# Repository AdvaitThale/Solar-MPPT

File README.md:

# Solar-MPPT
***************************************************************
The basic functionality of the device is based on previous generation Solar MPPTs, but it is fully autonomous (alpha ver) using ESP32 as microcontroller.
The file named `MPPT_Port-Xtensa.ino` code is final port of MPPT on the ESP32. Also, `MPPT_Port-328P.ino` shows an overview of how MPPT will work with ATMega328P microcontroller (with reduced functionality).It is equipped with 20*4 Character LCD (for device & energy status), Function Buttons, ESP32 Microcontroller, Solar Inlet, 30A FUSE, Sleep Mode, Webserver, 2 x PT-100(for Indoor & Outdoor Temp.), RS-232 Interface(at 9600),Program Serial(at 115200), Internal DIP Switches (for system configuration), Relay driven Outputs(for automation purpose), I/O for interfacing external sensors and automation purpose. The live status is displayed on LCD, the Webserver(at 192.168.1.1) to freely receive updates on PC/smartphone as well as the data log can be viewed via both RS-232 (DB9) or USB A Serial ports. Refer README.md and attached datasheets for furthur details on MPPT.

 IR Remote Keypad Hex Map:
  
        +------------------+              
        |              DC  |
        |                  |
        |  92    93    CC  |
        |  8E    8F    C8  |
        |  8A    8B    C4  |
        |  CF    87    82  |
        |                  |
        |  80    9C    85  |
        |  81  8C  DD  86  |
        |                  |
        |        CA        |
        |  88 99 CE C1 C5  |
        |        D2        |
        |                  |
        |  DA          D6  |
        |      98  95      |
        |                  |
        |  CD    91    D0  |
        |  8D  97  C3  83  |
        |                  |
        |  89  84  D9  96  |
        |                  |
        |     hathw@y      |
        +------------------+

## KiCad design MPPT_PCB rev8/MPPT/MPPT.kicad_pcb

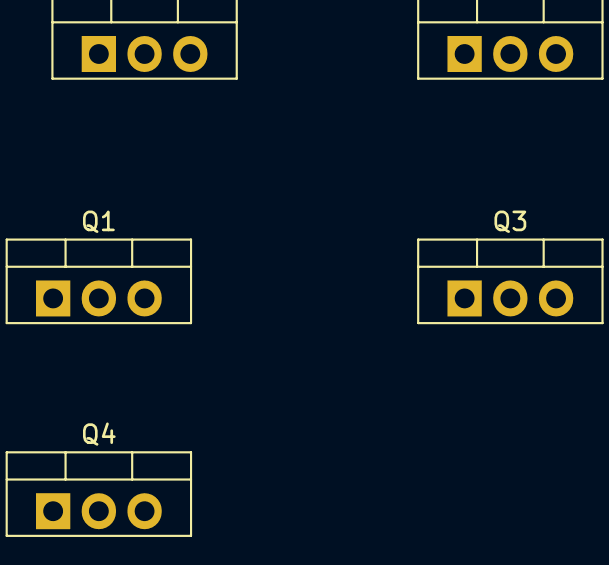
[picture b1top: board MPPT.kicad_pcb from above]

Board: 2 copper layers, 5 parts (0 on the bottom side), 5 nets, no tracks yet.

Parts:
Q1, Q2, Q3, Q4, Q5: IRLZ44N; TO-220-3_Vertical

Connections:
unnamed: Q1.2 (D), Q4.2 (D)
unnamed: Q1.3 (S), Q2.2 (D), Q3.2 (D)
unnamed: Q2.1 (G), Q3.1 (G), Q4.1 (G)
unnamed: Q2.3 (S), Q3.3 (S), Q5.3 (S)
unnamed: Q4.3 (S), Q5.2 (D)

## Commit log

2023-01-21 README (#1)
2023-01-21 README (#2)
2023-01-21 Bugs & Fixes (#2)
2023-01-22 README (#3)
2023-01-23 Bugs & Fixes (#3)
2023-01-25 Report (#2)
2023-01-27 Datasheets (#2)
    c2073
2023-01-27 Datasheets (#3)
    KIA78R
2023-01-27 Datasheets (#4)
    STR-W6754F
2023-01-27 Datasheets (#5)
    LA78040B
2023-01-27 Datasheets (#6)
    MD1803DFX
2023-01-29 README (#4)
2023-01-29 README (#5)
2023-01-29 README (#6)
2023-01-29 Bugs & Fixes (#4)
2023-02-02 Report (#3)
2023-02-05 README (#7)
2023-02-05 Bugs & Fixes (#5)
2023-02-05 Bugs & Fixes (#6)
2023-02-05 Config (#6)
2023-02-11 PCB (#3)
2023-02-11 Config (#7)
2023-02-12 Bugs & Fixes (#7)
2023-02-12 Config (#8)
2023-02-12 Config (#9)
2023-02-13 Config (#10)
2023-02-13 Config (#11)
2023-02-14 Report (#4)
2023-02-15 Bugs & Fixes (#8)
2023-02-17 Config (#12)
2023-02-18 Config (#13)
2023-02-18 Mixer (#1)
2023-02-18 Mixer (#2)
2023-02-19 Mixer (#3)
2023-02-20 Config (#14)
2023-02-20 Config (#15)
2023-02-20 Config (#16)
2023-02-20 Bugs & Fixes (#9)
2023-02-21 Bugs & Fixes (#10)
2023-02-21 Config (#17)
    IR -> Done
2023-02-22 Config (#18)
2023-02-22 Bugs & Fixes (#11)
2023-02-24 README (#8)
2023-02-24 Config (#19)
2023-02-24 Config (#20)
2023-02-24 Bugs & Fixes (#12)
2023-02-27 README (#9)
2023-02-28 PCB (#4)
2023-03-01 PCB (#5)
2023-03-02 PCB (#6)
2023-03-03 PCB (#7)
2023-03-08 PCB (#8)
2023-03-13 PCB (#9)
2023-03-13 Bugs & Fixes (#13)
2023-03-14 Bugs & Fixes (#14)
2023-03-15 Bugs & Fixes (#15)
2023-03-15 PCB (#10)
2023-03-16 PCB (#11)
2023-03-16 README (#10)
2023-03-16 README (#11)
2023-03-16 PCB (#12)
2023-03-16 PCB (#13)
2023-03-16 PCB (#14)
2023-03-17 PCB (#15)
2023-03-17 PCB (#16)
2023-03-17 PCB (#17)
2023-03-17 PCB (#18)
2023-03-17 Config (#21)
2023-03-18 PCB (#19)
2023-03-18 PCB (#20)
2023-03-20 PCB (#21)
2023-03-20 README (#12)
2023-03-20 PCB (#22)
2023-03-21 PCB (#23)
2023-03-21 PCB (#24)
2023-03-22 PCB (#25)
2023-03-23 PCB (#26)
2023-03-23 PCB (#27)
2023-03-23 PCB (#28)
    Inverter
2023-03-24 PCB (#29)
2023-03-26 PCB (#30)
2023-03-27 PCB (#31)
2023-03-27 Report (#5)
2023-03-28 PCB (#32)
2023-03-28 PCB (#33)
2023-03-29 PCB (#34)
2023-03-30 PCB (#35)
2023-03-30 PCB (#36)
2023-03-31 PCB (#37)
2023-03-31 PCB (#38)
2023-03-31 PCB (#39)
2023-03-31 PCB (#40)
2023-03-31 PCB (#41)
2023-03-31 PCB (#42)
2023-04-01 PCB (#43)
2023-04-02 PCB (#44)
2023-04-02 PCB (#45)
2023-04-02 PCB (#46)
2023-04-03 PCB (#47)
2023-04-04 PCB (#48)
2023-04-05 PCB (#49)
2023-04-06 PCB (#50)
2023-04-07 PCB (#51)
2023-04-07 PCB (#52)
2023-04-08 PCB (#53)
2023-04-09 PCB (#54)
2023-04-12 PCB (#55)
2023-04-12 PCB (#56)
2023-04-13 PCB (#57)
2023-04-14 PCB (#58)
2023-04-14 PCB (#59)
2023-04-15 PCB (#60)
2023-04-15 PCB (#61)
2023-04-16 PCB (#62)
2023-04-17 PCB (#63)
2023-04-18 PCB (#64)
2023-04-19 PCB (#65)
2023-04-19 PCB (#66)
2023-04-20 PCB (#67)
2023-04-21 PCB (#68)
2023-04-21 PCB (#69)
2023-04-21 PCB (#70)
2023-04-21 PCB (#71)
2023-04-21 PCB (#72)
2023-04-21 PCB (#73)
2023-04-22 PCB (#74)
2023-04-22 PCB (#75)
2023-04-22 PCB (#76)
2023-04-22 PCB (#77)
2023-04-22 PCB (#78)
2023-04-22 PCB (#79)
2023-04-23 PCB (#80)
2023-04-23 PCB (#81)
2023-04-23 PCB (#82)
2023-04-23 PCB (#83)
2023-04-23 PCB (#84)
2023-04-24 PCB (#85)
2023-04-24 PCB (#86)
2023-04-25 PCB (#87)
2023-04-25 PCB (#88)
2023-04-25 PCB (#89)
2023-04-25 PCB (#90)
2023-04-26 PCB (#91)
2023-04-26 PCB (#92)
2023-05-01 PCB (#93)
2023-05-01 Report (#6)
2023-05-01 Bugs & Fixes (#16)
2023-05-01 Report (#7)
2023-05-07 PCB (#94)
2023-05-07 Bugs & Fixes (#17)
2023-05-07 Config (#22)
2023-05-08 PCB (#95)
2023-05-08 Config (#23)
2023-05-10 Config (#24)
2023-05-12 Config (#25)
2023-05-12 Config (#26)
2023-05-12 Config (#27)
2023-05-12 Config (#28)
2023-05-13 Bugs & Fixes (#18)
2023-05-13 Bugs & Fixes (#19)
2023-05-13 Bugs & Fixes (#20)
2023-05-13 Config (#29)
2023-05-13 Bugs & Fixes (#21)
2023-05-14 Config (#30)
2023-05-14 Config (#31)
2023-05-14 Bugs & Fixes (#22)
2023-05-14 Bugs & Fixes (#23)
2023-05-14 Bugs & Fixes (#24)
2023-05-14 Bugs & Fixes (#25)
2023-05-14 Bugs & Fixes (#26)
2023-05-16 Bugs & Fixes (#27)
2023-05-16 PCB (#96)
2023-05-16 Bugs & Fixes (#28)
2023-05-17 Report (#8)
2023-05-17 Bugs & Fixes (#29)
2023-05-17 Config (#32)
2023-05-17 Config (#33)
2023-05-17 Bugs & Fixes (#30)
2023-05-17 Datasheets (#7)
2023-05-17 Datasheets (#8)
2023-05-17 Datasheets (#9)
2023-05-18 Bugs & Fixes (#31)
2023-05-18 PCB (#97)
2023-05-18 Report(#9)
2023-05-18 Report (#10)
2023-05-19 Config (#34)
2023-05-19 Config (#35)
2023-05-19 Config (#36)
2023-05-19 Report (#11)
2023-05-19 Report (#12)
2023-05-19 Report (#13)
2023-05-19 Bugs & Fixes (#32)
2023-05-20 Report (#14)
2023-05-25 Report (#15)
2023-05-25 Report (#16)
2023-05-25 Report (#17)
2023-05-25 Webserver (#2)
2023-05-25 Bugs & Fixes (#33)
2023-05-26 Bugs & Fixes (#34)
2023-07-10 Bugs & Fixes (#35)
2023-11-27 Bugs & Fixes (#36)
2023-11-27 PCB (#98)
